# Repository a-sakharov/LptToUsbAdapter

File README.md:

# LptToUsbAdapter

Solution for connecting old LPT device to modern PC via USB

Directory info:

- Schematics - schematics of USBLPT hardware using AVR MCU.
- Firmware - source code for AVR MCU firmware.
- LptToUsbAdapter - source code for host software, this example optimized for "Orange" programmer, but can easily be ported to work with other software.

Detailed desctiption: https://habr.com/ru/articles/727468/

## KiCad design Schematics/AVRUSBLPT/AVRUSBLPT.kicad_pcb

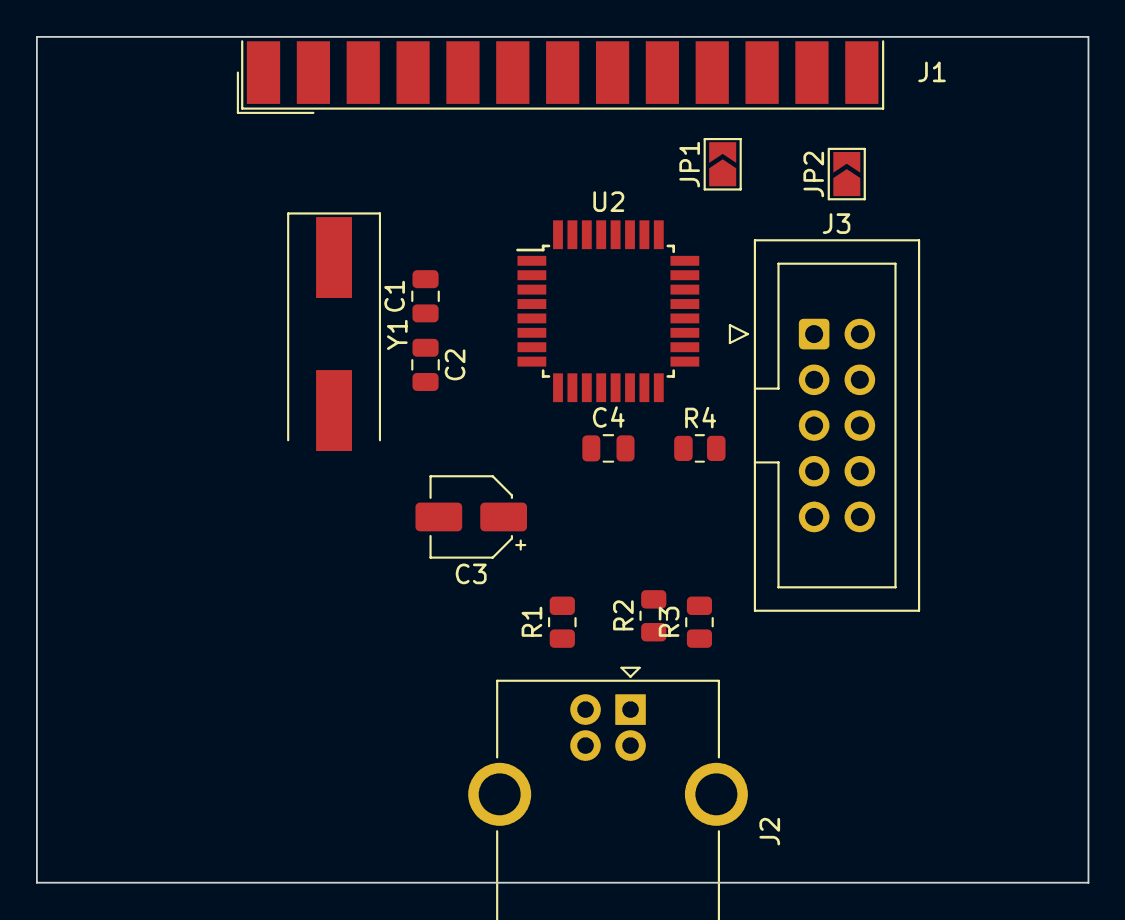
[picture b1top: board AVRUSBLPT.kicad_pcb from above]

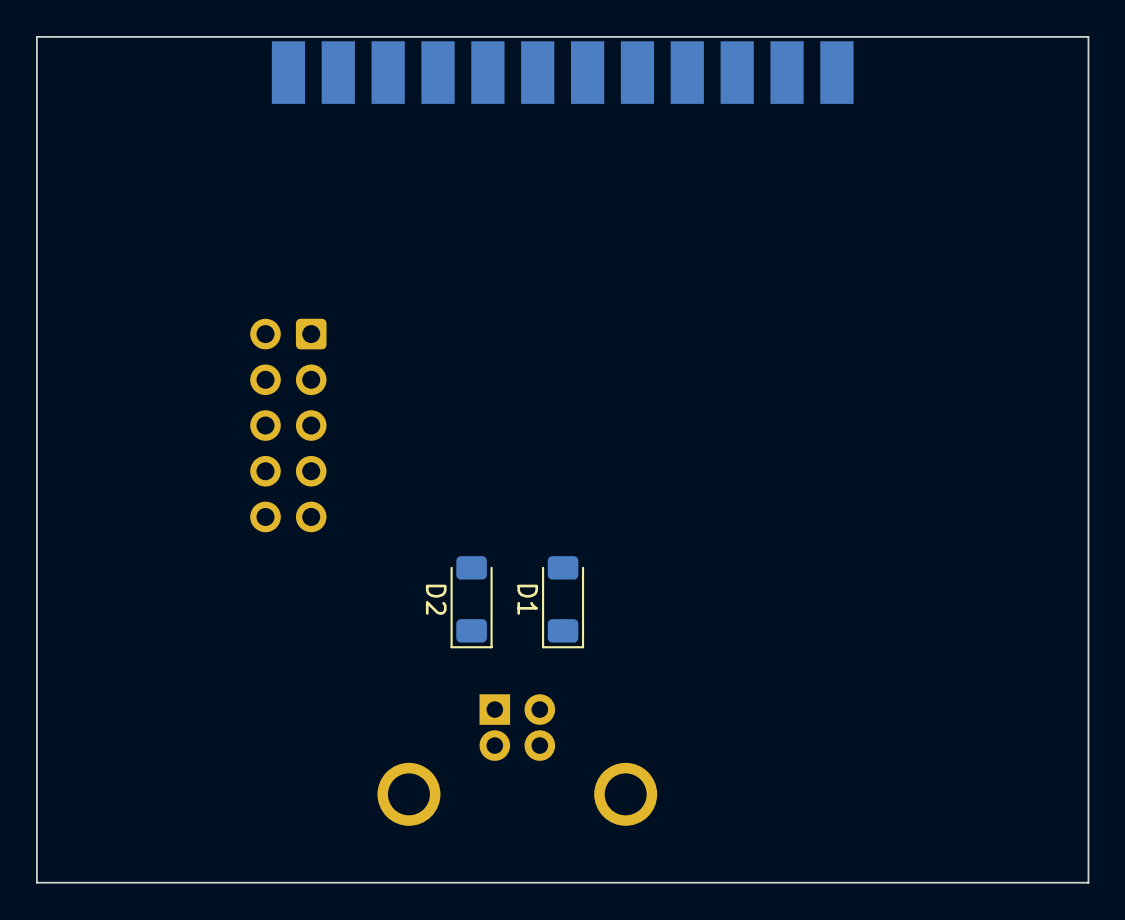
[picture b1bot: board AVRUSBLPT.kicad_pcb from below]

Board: 2 copper layers, 58.4 x 47.0 mm, 17 parts (2 on the bottom side), 29 nets, no tracks yet.

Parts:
C1, C2: 18pF; C_0805_2012Metric
C3: 4.7uF; CP_Elec_4x5.4
C4: 100nF; C_0805_2012Metric
D1, D2: 3.6; D_MiniMELF
J1: DB25_Receptacle; DSUB-25_Female_EdgeMount_P2.77mm
J2: USB_B; USB_B_OST_USB-B1HSxx_Horizontal
J3: IDC10; IDC-Header_2x05_P2.54mm_Vertical
JP1, JP2: SolderJumper-2_P1.3mm_Open_TrianglePad1.0x1.5mm
R1, R2: 68; R_0805_2012Metric
R3: 1.5k; R_0805_2012Metric
R4: 4.7k; R_0805_2012Metric
U2: ATmega8A-A; TQFP-32_7x7mm_P0.8mm
Y1: 16MHz; Crystal_SMD_HC49-SD

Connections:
/ACK: J1.10, JP1.2 (B)
/AVR_DM: R2.2, U2.2 (PD4)
/AVR_DP: R1.2, U2.32 (PD2)
/AVR_RESET: J3.5 (~RST), R4.1, U2.29 (PC6/~RESET)
/D0: J1.2, U2.11 (PD7)
/D1: J1.3, U2.10 (PD6)
/D2: J1.4, U2.9 (PD5)
/D3: J1.5, U2.1 (PD3)
/D4: J1.6, U2.31 (PD1)
/D5: J1.7, U2.30 (PD0)
/D6: J1.8, U2.28 (PC5)
/D7: J1.9, U2.27 (PC4)
/ERROR: J1.15, U2.25 (PC2)
/GND: C1.1, C2.1, C3.2, C4.1, D1.2 (A), D2.2 (A), J1.18, J1.19, J1.20, J1.21, J1.22, J1.23, J1.24, J1.25, J2.4 (GND), J2.5 (Shield), J3.4 (GND), J3.6 (GND), J3.8 (GND), J3.10 (GND), U2.3 (GND), U2.5 (GND), U2.21 (AGND)
/MISO: J3.9 (MISO), JP1.1 (A), U2.16 (PB4)
/MOSI: J3.1 (MOSI), U2.15 (PB3)
/PAPER_OUT: J1.12, U2.12 (PB0)
/RESET: J1.16, U2.26 (PC3)
/SCK: J3.7 (SCK), JP2.1 (A), U2.17 (PB5)
/SELECT: J1.13, JP2.2 (B)
/VBUS: C3.1, C4.2, J2.1 (VBUS), J3.2 (VCC), R3.2, R4.2, U2.4 (VCC), U2.6 (VCC), U2.18 (AVCC), U2.20 (AREF)
/nBUSY: J1.11, U2.13 (PB1)
/nLINE_FEED: J1.14, U2.24 (PC1)
/nSELECT_PRINTER: J1.17, U2.14 (PB2)
/nSTROBE: J1.1, U2.23 (PC0)
unnamed: D1.1 (K), J2.3 (D+), R1.1
unnamed: D2.1 (K), J2.2 (D-), R2.1, R3.1
unnamed: C1.2, U2.7 (PB6/XTAL1), Y1.1
unnamed: C2.2, U2.8 (PB7/XTAL2), Y1.2

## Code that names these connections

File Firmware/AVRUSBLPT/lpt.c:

/*
 * lpt.c
 *
 * Created: 2023-03-10 19:22:21
 *  Author: a.sakharov
 */ 

#include "lpt.h"
#include <avr/io.h>
#include <stdbool.h>
#include <util/delay.h>


/*
| Net             | Pin |
|-----------------|-----|
| D0              | PC4 |
| D1              | PC3 |
| D2              | PC2 |
| D3              | PC1 |
| D4              | PC0 |
| D5              | PB5 |
| D6              | PB4 |
| D7              | PB3 |
|                 |     |
| nSTROBE         | PC5 |
| nLINE_FEED      | PD0 |
| RESET           | PD3 |
| nSELECT_PRINTER | PD5 |
|                 |     |
| ERROR           | PD1 |
| ACK             | PB2 |
| nBUSY           | PB1 |
| PAPER_OUT       | PD6 |
| SELECT          | PD7 |
*/

//status
#define GET_ERROR()     (PIND & _BV(1))
#define GET_ACK()       (PINB & _BV(2))
#define GET_nBUSY()     (PINB & _BV(1))
#define GET_PAPER_OUT() (PIND & _BV(6))
#define GET_SELECT()    (PIND & _BV(7))

#define IN_ERROR()      (DDRD &= ~_BV(1))
#define IN_ACK()        (DDRB &= ~_BV(2))
#define IN_nBUSY()      (DDRB &= ~_BV(1))
#define IN_PAPER_OUT()  (DDRD &= ~_BV(6))
#define IN_SELECT()     (DDRD &= ~_BV(7))

//control
#define SET_nSTROBE(x)          if(x) PORTC |= _BV(5); else PORTC &= ~_BV(5)
#define SET_nLINE_FEED(x)       if(x) PORTD |= _BV(0); else PORTD &= ~_BV(0)
#define SET_RESET(x)            if(x) PORTD |= _BV(3); else PORTD &= ~_BV(3)
#define SET_nSELECT_PRINTER(x)  if(x) PORTD |= _BV(5); else PORTD &= ~_BV(5)

#define OUT_nSTROBE()          DDRC |= _BV(5)
#define OUT_nLINE_FEED()       DDRD |= _BV(0)
#define OUT_RESET()            DDRD |= _BV(3)
#define OUT_nSELECT_PRINTER()  DDRD |= _BV(5)

//data
#define OUT_D0() DDRC |= _BV(4)
#define OUT_D1() DDRC |= _BV(3)
#define OUT_D2() DDRC |= _BV(2)
#define OUT_D3() DDRC |= _BV(1)
#define OUT_D4() DDRC |= _BV(0)
#define OUT_D5() DDRB |= _BV(5)
#define OUT_D6() DDRB |= _BV(4)
#define OUT_D7() DDRB |= _BV(3)

#define IN_D0() (DDRC &= ~_BV(4))
#define IN_D1() (DDRC &= ~_BV(3))
#define IN_D2() (DDRC &= ~_BV(2))
#define IN_D3() (DDRC &= ~_BV(1))
#define IN_D4() (DDRC &= ~_BV(0))
#define IN_D5() (DDRB &= ~_BV(5))
#define IN_D6() (DDRB &= ~_BV(4))
#define IN_D7() (DDRB &= ~_BV(3))

#define OUT_DATA() OUT_D0(),OUT_D1(),OUT_D2(),OUT_D3(),OUT_D4(),OUT_D5(),OUT_D6(),OUT_D7()
#define IN_DATA()  IN_D0(),IN_D1(),IN_D2(),IN_D3(),IN_D4(),IN_D5(),IN_D6(),IN_D7()

#define SET_D0(x) if(x) PORTC |= _BV(4); else PORTC &= ~_BV(4)
#define SET_D1(x) if(x) PORTC |= _BV(3); else PORTC &= ~_BV(3)
#define SET_D2(x) if(x) PORTC |= _BV(2); else PORTC &= ~_BV(2)
#define SET_D3(x) if(x) PORTC |= _BV(1); else PORTC &= ~_BV(1)
#define SET_D4(x) if(x) PORTC |= _BV(0); else PORTC &= ~_BV(0)
#define SET_D5(x) if(x) PORTB |= _BV(5); else PORTB &= ~_BV(5)
#define SET_D6(x) if(x) PORTB |= _BV(4); else PORTB &= ~_BV(4)
#define SET_D7(x) if(x) PORTB |= _BV(3); else PORTB &= ~_BV(3)

#define GET_D0() (PINC & _BV(4))
#define GET_D1() (PINC & _BV(3))
#define GET_D2() (PINC & _BV(2))
#define GET_D3() (PINC & _BV(1))
#define GET_D4() (PINC & _BV(0))
#define GET_D5() (PINB & _BV(5))
#define GET_D6() (PINB & _BV(4))
#define GET_D7() (PINB & _BV(3))


static volatile AVRLPT_MODE ActiveMode;

//store last written values
static volatile uint8_t PCON;
static volatile uint8_t PDATA;
static volatile uint8_t PSTAT;
static volatile uint8_t ADDSTR;
static volatile uint8_t DATASTR;

static uint8_t DataGet()
{
    uint8_t value = 0;
    
    if(GET_D0()) value |= _BV(0);
    if(GET_D1()) value |= _BV(1);
    if(GET_D2()) value |= _BV(2);
    if(GET_D3()) value |= _BV(3);
    if(GET_D4()) value |= _BV(4);
    if(GET_D5()) value |= _BV(5);
    if(GET_D6()) value |= _BV(6);
    if(GET_D7()) value |= _BV(7);
    
    return value;
}

static void DataSet(uint8_t value)
{
    SET_D0(value & _BV(0));
    SET_D1(value & _BV(1));
    SET_D2(value & _BV(2));
    SET_D3(value & _BV(3));
    SET_D4(value & _BV(4));
    SET_D5(value & _BV(5));
    SET_D6(value & _BV(6));
    SET_D7(value & _BV(7));
}

static bool EppWrite(uint8_t data, bool AddrMode)
{
    bool success = true;
    
    if(GET_nBUSY() != 0)
    {
        return false;
    }
    
    //setup
    OUT_DATA();
    
    //perform
    SET_nSTROBE(0); //write=0
    DataSet(data); //DATA set
    
    SET_nLINE_FEED(AddrMode==true); //set data strobe 
    SET_nSELECT_PRINTER(AddrMode==false); //set adddr strobe
    
    _delay_us(1);
    
    //waiting for WAIT#
    uint8_t timeout = 10;
    while(timeout != 0 && GET_nBUSY() == 0)
    {
        timeout--;
        _delay_us(1);
    }
    
    if(GET_nBUSY() == 0)
    {
        success = false;
    }
    
    SET_nLINE_FEED(1); //set data strobe
    SET_nSELECT_PRINTER(1); //set adddr strobe
    SET_nSTROBE(1); //write=1
    
    //unsetup
    if(!(PCON & _BV(5)))
    {
        //pdata output
        OUT_DATA();
    }
    else
    {
        //pdata input
        IN_DATA();
    }
    
    return success;
}

static bool EppRead(uint8_t *data, bool AddrMode)
{
    bool success = true;
    
    if(GET_nBUSY() != 0)
    {
        return false;
    }
        
    //setup
    IN_DATA();
    
    //perform
    SET_nSTROBE(1); //write=1
    
    SET_nLINE_FEED(AddrMode==true); //set data strobe
    SET_nSELECT_PRINTER(AddrMode==false); //set adddr strobe
    
    //waiting for WAIT#
    uint8_t timeout = 10;
    while(timeout != 0 && GET_nBUSY() == 0)
    {
        timeout--;
        _delay_us(1);
    }
    
    if(GET_nBUSY() == 0)
    {
        success = false;
    }
    else
    {
        *data = DataGet();
    }
    
    SET_nLINE_FEED(1); //set data strobe
    SET_nSELECT_PRINTER(1); //set addr strobe
    
    //unsetup
    if(GET_nBUSY() != 0)
    {
        PCON |= _BV(5); //bad idea but maybe safe
    }
    
    return success;
}

void LPT_Init()
{
    if((ActiveMode == LPT_MODE_LEGACY) || !(PCON & _BV(5)))
    {
        //pdata output
        OUT_DATA();
    }
    else
    {
        //pdata input
        IN_DATA();
    }
    
    //conrol always output
    OUT_nSTROBE();
    OUT_nLINE_FEED();
    OUT_RESET();
    OUT_nSELECT_PRINTER();
    
    //status always input
    IN_ERROR();
    IN_ACK();
    IN_nBUSY();
    IN_PAPER_OUT();
    IN_SELECT();
}

void LPT_SetMode(AVRLPT_MODE mode)
{
    if(mode == ActiveMode)
    {
        return;
    }
    
    ActiveMode = mode;
    
    LPT_Init();
}

void LPT_SetReg(AVRLPT_REG reg, uint8_t value)
{
    switch(reg)
    {
        case AVRLPT_REG_PDATA:
        if((ActiveMode == LPT_MODE_LEGACY) || !(PCON & _BV(5)))//if DATA is output 
        {
            DataSet(value);
            PDATA = value;
        }
        break;
        
        case AVRLPT_REG_PSTAT:
        //PSTAT = value; //read-only reg
        break;
        
        case AVRLPT_REG_PCON:
        if(ActiveMode == LPT_MODE_LEGACY)
        {
            PCON = value & 0x1F;
        }
        else
        {
            PCON = value & 0x3F;
            if(PCON & _BV(5))
            {
                IN_DATA();
            }
            else
            {
                OUT_DATA();
            }
        }
        
        SET_nSTROBE(!(value & _BV(0)));//inverted
        SET_nLINE_FEED(!(value & _BV(1)));//inverted
        SET_RESET(value & _BV(2));
        SET_nSELECT_PRINTER(!(value & _BV(3)));//inverted
        break;
        
        case AVRLPT_REG_ADDSTR:
        if(ActiveMode == LPT_MODE_EPP)
        {
            ADDSTR = value;
            if(!EppWrite(ADDSTR, true))
            {
                PSTAT |= 1;
            }
        }
        break;
        
        case AVRLPT_REG_DATASTR:
        if(ActiveMode == LPT_MODE_EPP)
        {
            ADDSTR = value;
            if(!EppWrite(ADDSTR, false))
            {
                PSTAT |= 1;
            }
        }

        break;
    }
}

uint8_t LPT_GetReg(AVRLPT_REG reg)
{
    uint8_t value = 0;
    
    switch(reg)
    {
        case AVRLPT_REG_PDATA:
        if((ActiveMode == LPT_MODE_LEGACY) || !(PCON & _BV(5)))//if DATA is output
        {
            return PDATA;
        }
        else
        {
            return DataGet();
        }
        break;
        
        case AVRLPT_REG_PSTAT:
        value = PSTAT & 0x01; //save time-out bit
        PSTAT = 0; //clear time-out bit
        if(!GET_nBUSY()) value |= _BV(7);//inverted
        if(GET_ACK()) value |= _BV(6);
        if(GET_PAPER_OUT()) value |= _BV(5);
        if(GET_SELECT()) value |= _BV(4);
        if(GET_ERROR()) value |= _BV(3);
        return value;
        break;
        
        case AVRLPT_REG_PCON:
        return PCON;
        break;
        
        case AVRLPT_REG_ADDSTR:
        if(!EppRead(&value, true))
        {
            PSTAT |= 0x01;
        }
        return value;
        break;
        
        case AVRLPT_REG_DATASTR:
        if(!EppRead(&value, false))
        {
            PSTAT |= 0x01;
        }
        return value;
        break;
    }
    
    return 0;
}

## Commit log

2023-03-11 Initial commit, MVP
2023-03-15 Added mempatch mode
2023-03-15 Added license and dummy readme
2023-03-15 Added schematic as an image
2023-03-15 Fixed inaccurate project settings
2023-05-17 Added link to habr.com article, changed PIC to 4153, added compatibility with C++ compiler for AVRLPT lib
2023-05-18 Renamed AVRLPT to USBLPT inside host software for less inconvenience
2023-05-18 Rest of project/files inside host software moved from AVRLPT to USBLPT
2023-11-08 V3 indev
2023-11-08 Huge renaming (got rig of those o-m-e-g-a-s)
2023-11-08 A bit more renaming and restructuring
2023-11-08 Readme updated
2023-11-08 Another readme update
2023-11-21 Almost everything around USB was rewritten, also USBLPT enumeration support added
2023-11-21 Just noticed that LptPortAccessDemo.c missing from repo
2023-11-22 Fixed bug in UsbLpt enumeration Added debug code Bit of renaming
2023-12-13 Bug fixed INI settings support New hardware support
2023-12-13 Introduced new settings in INI file Fixed issues found by PVS-Studio
2023-12-13 Functions cut to other functions Updating settings only if change was made
2023-12-13 Settings handling changed
2023-12-13 Bit of settings naming changed
2023-12-13 *fix
2023-12-13 Some code moved to CommonCode.c
2023-12-13 Those CommonCode mentioned before. And added file that was lost before somehow
2023-12-13 A bit of update. Logging speed up, all settings work now.
2023-12-24 Communication through pipes implemented
2024-01-11 Update procedure and USBLPT3r0 firmware added
2024-01-12 Fixed typo, updated firmware
2024-03-03 Added windows 7 driver binaries and configuration
2024-05-19 Добавил билд прошивки для AVR
2024-10-02 Added missing dependencies
